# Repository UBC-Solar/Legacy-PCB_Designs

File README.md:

# PCB_Designs
Eagle files for PCBs designed for Raven

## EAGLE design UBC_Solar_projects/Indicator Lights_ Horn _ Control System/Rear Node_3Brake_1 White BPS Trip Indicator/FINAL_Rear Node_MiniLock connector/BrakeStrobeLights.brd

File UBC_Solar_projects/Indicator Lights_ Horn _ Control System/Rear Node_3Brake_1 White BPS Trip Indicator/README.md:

Rear Node Controls:
	1. 3 Brake Lights
	2. 1 White Strobe light (BPS TRIP INDICATOR)

NOTE:
	-PCB Holes are too close to sides
	-PCB Name should be on the buttom side

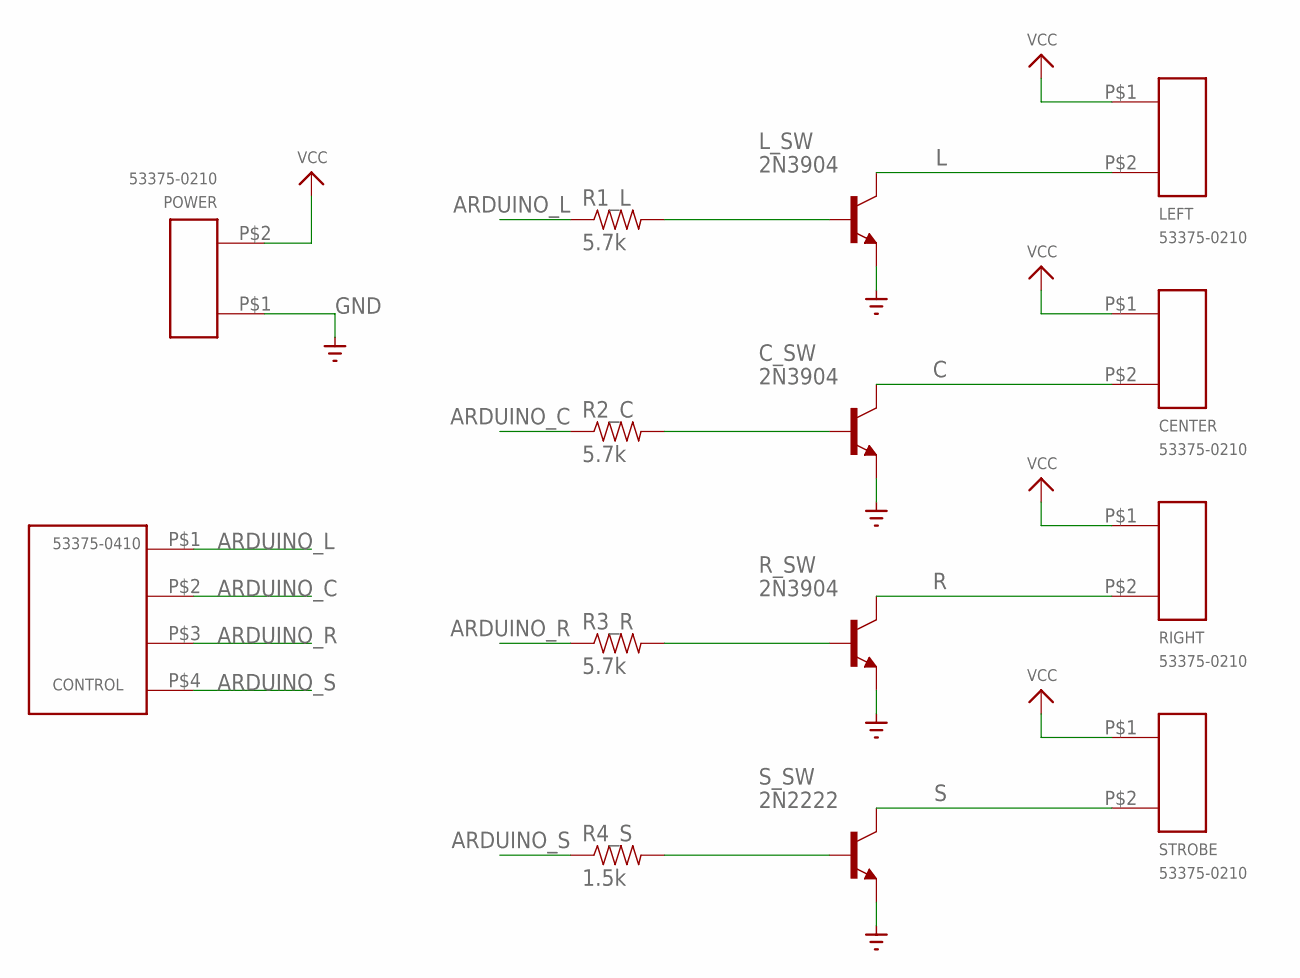
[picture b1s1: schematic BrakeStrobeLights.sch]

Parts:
CENTER: 53375-0210; 53375-0210-MINI-LOCK
CONTROL: 53375-0410; 53375-0410-MINI-LOCK
C_SW: 2N3904; TO92
LEFT: 53375-0210; 53375-0210-MINI-LOCK
L_SW: 2N3904; TO92
POWER: 53375-0210; 53375-0210-MINI-LOCK
R1_L, R2_C, R3_R: 5.7k; 1/6W-RES
R4_S: 1.5k; 1/6W-RES
RIGHT: 53375-0210; 53375-0210-MINI-LOCK
R_SW: 2N3904; TO92
STROBE: 53375-0210; 53375-0210-MINI-LOCK
S_SW: 2N2222; TO92-EBC-OVAL

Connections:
ARDUINO_C: CONTROL.P$2 (2), R2_C.1
ARDUINO_L: CONTROL.P$1 (1), R1_L.1
ARDUINO_R: CONTROL.P$3 (3), R3_R.1
ARDUINO_S: CONTROL.P$4 (4), R4_S.1
C: CENTER.P$2 (2), C_SW.1 (C)
GND: C_SW.3 (E), L_SW.3 (E), POWER.P$1 (1), R_SW.3 (E), S_SW.E
L: LEFT.P$2 (2), L_SW.1 (C)
unnamed: R3_R.2, R_SW.2 (B)
unnamed: C_SW.2 (B), R2_C.2
unnamed: R4_S.2, S_SW.B
unnamed: L_SW.2 (B), R1_L.2
R: RIGHT.P$2 (2), R_SW.1 (C)
S: STROBE.P$2 (2), S_SW.C
VCC: CENTER.P$1 (1), LEFT.P$1 (1), POWER.P$2 (2), RIGHT.P$1 (1), STROBE.P$1 (1)

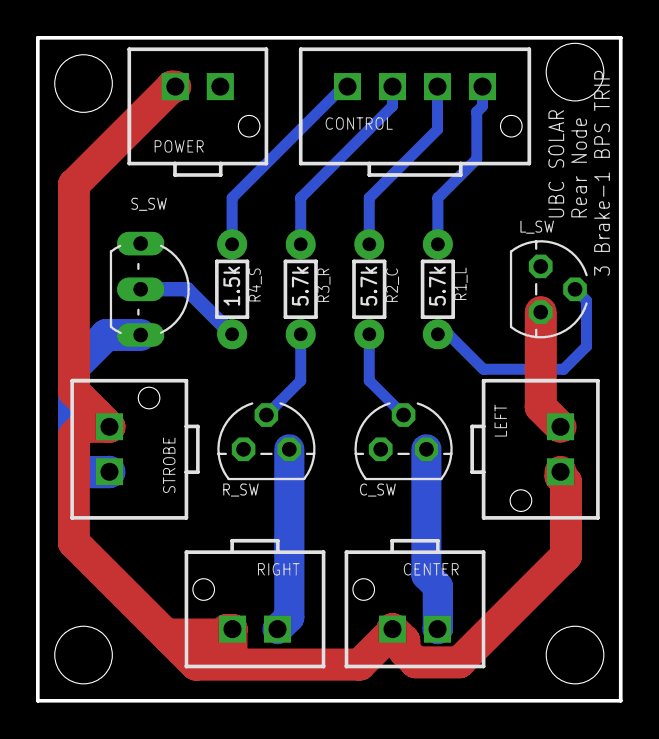
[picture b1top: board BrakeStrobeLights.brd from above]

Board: 2 copper layers, 32.4 x 36.8 mm, 14 parts (0 on the bottom side), 14 nets.

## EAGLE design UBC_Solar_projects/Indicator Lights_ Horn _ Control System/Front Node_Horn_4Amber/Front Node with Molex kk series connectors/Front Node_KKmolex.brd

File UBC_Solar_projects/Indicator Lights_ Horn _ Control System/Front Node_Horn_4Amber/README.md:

Front Node Controls:
	1. 4 Amber Lights
	2. Horn

NOTE:
	-PCB Holes are too close to sides
	-PCB Name should be on the buttom side

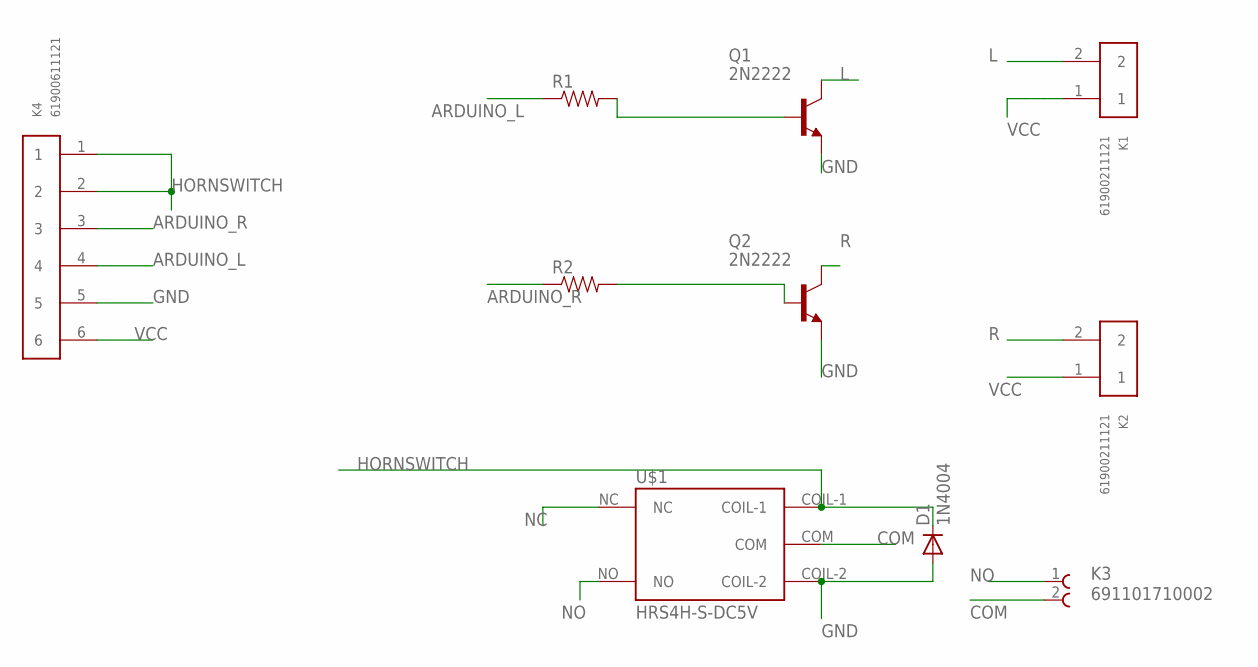
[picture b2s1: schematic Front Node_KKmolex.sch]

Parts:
D1: 1N4004; DO41-10
K1, K2: 61900211121
K3: 691101710002
K4: 61900611121
Q1, Q2: 2N2222; TO18
R1, R2: RESISTORPTH-1/4W; AXIAL-0.4
U$1: HRS4H-S-DC5V; RELAY

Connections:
ARDUINO_L: K4.4, R1.P$1 (1)
ARDUINO_R: K4.3, R2.P$1 (1)
COM: K3.2, U$1.COM
GND: D1.A, K4.5, Q1.1 (E), Q2.1 (E), U$1.COIL-2
HORNSWITCH: D1.C, K4.1, K4.2, U$1.COIL-1
L: K1.2, Q1.3 (C)
unnamed: Q2.2 (B), R2.P$2 (2)
unnamed: Q1.2 (B), R1.P$2 (2)
NC: U$1.NC
NO: K3.1, U$1.NO
R: K2.2, Q2.3 (C)
VCC: K1.1, K2.1, K4.6

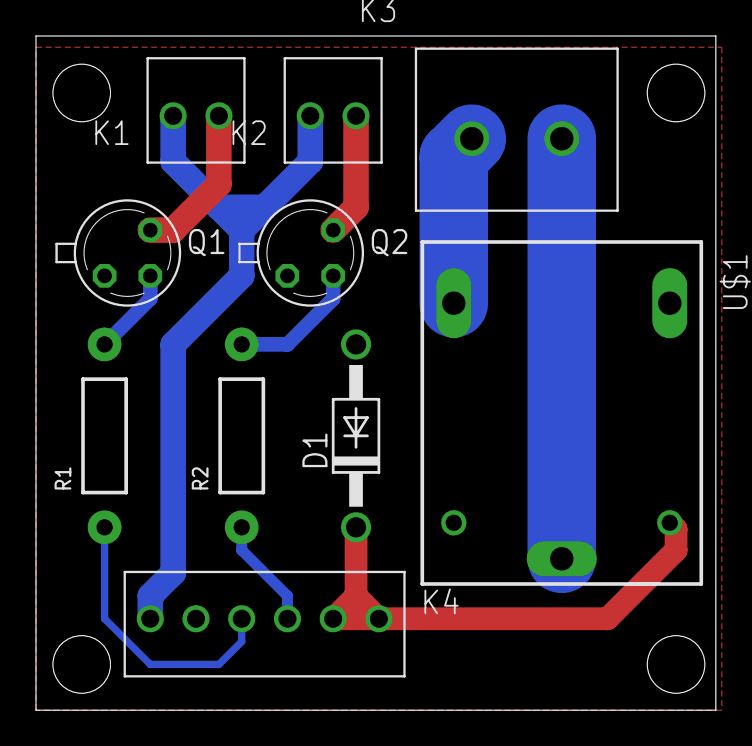
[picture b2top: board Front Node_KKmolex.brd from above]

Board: 2 copper layers, 37.8 x 37.5 mm, 10 parts (0 on the bottom side), 11 nets.

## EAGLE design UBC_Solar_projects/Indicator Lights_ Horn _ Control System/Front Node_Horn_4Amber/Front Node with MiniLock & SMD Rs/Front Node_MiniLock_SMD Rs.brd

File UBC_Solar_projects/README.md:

UBC Solar Projects.

Add this directory to your eagle project directory:
  1. choose "options" tab on eagle
  2. "Directory"
  3. Add the destination of this folder in your computer to the "Projects" list
  4. use semicolon ; to separate directories from each other when you have more than 1(in this case eagle default workspace and this folder)

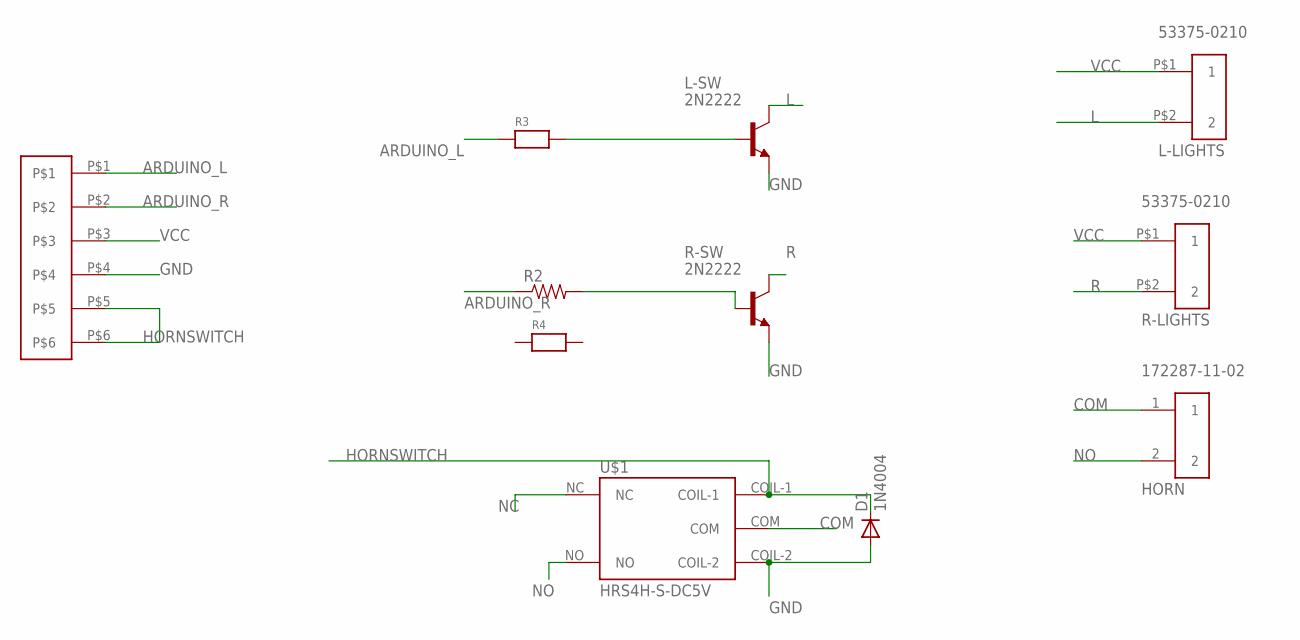
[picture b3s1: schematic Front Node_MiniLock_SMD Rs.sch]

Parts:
ARDUINO: 53375-0610; 53375-0610-MINI-LOCK
D1: 1N4004; DO41-10
HORN: 172287-11-02; 172287-ULTRA-FIT
L-LIGHTS: 53375-0210; 53375-0210-MINI-LOCK
L-SW: 2N2222; TO18
R2: RESISTORPTH-1/4W; AXIAL-0.4
R3, R4: RESISTOR1206; 1206
R-LIGHTS: 53375-0210; 53375-0210-MINI-LOCK
R-SW: 2N2222; TO18
U$1: HRS4H-S-DC5V; RELAY

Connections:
ARDUINO_L: ARDUINO.P$1, R3.1
ARDUINO_R: ARDUINO.P$2, R2.P$1 (1)
COM: HORN.1, U$1.COM
GND: ARDUINO.P$4, D1.A, L-SW.1 (E), R-SW.1 (E), U$1.COIL-2
HORNSWITCH: ARDUINO.P$5, ARDUINO.P$6, D1.C, U$1.COIL-1
L: L-LIGHTS.P$2 (2), L-SW.3 (C)
unnamed: R2.P$2 (2), R-SW.2 (B)
unnamed: L-SW.2 (B), R3.2
NC: U$1.NC
NO: HORN.2, U$1.NO
R: R-LIGHTS.P$2 (2), R-SW.3 (C)
VCC: ARDUINO.P$3, L-LIGHTS.P$1 (1), R-LIGHTS.P$1 (1)

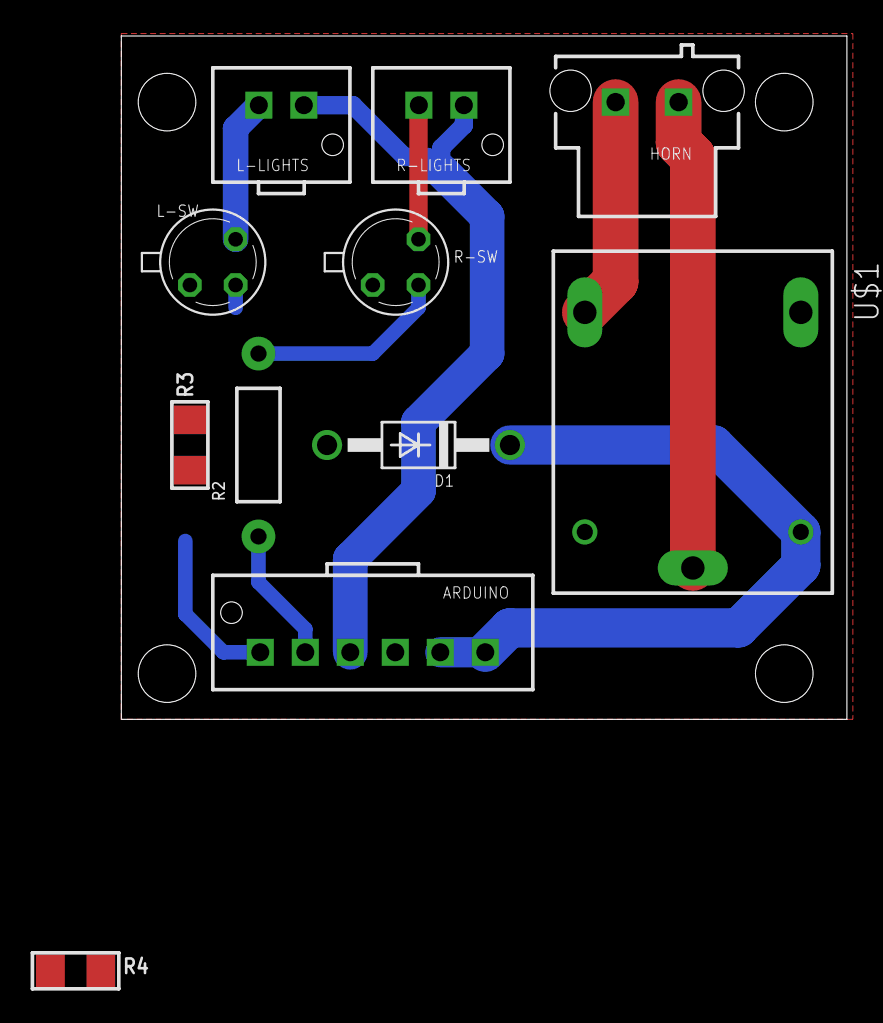
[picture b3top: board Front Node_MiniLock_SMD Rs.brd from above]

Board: 2 copper layers, 40.3 x 38.0 mm, 11 parts (0 on the bottom side), 11 nets.

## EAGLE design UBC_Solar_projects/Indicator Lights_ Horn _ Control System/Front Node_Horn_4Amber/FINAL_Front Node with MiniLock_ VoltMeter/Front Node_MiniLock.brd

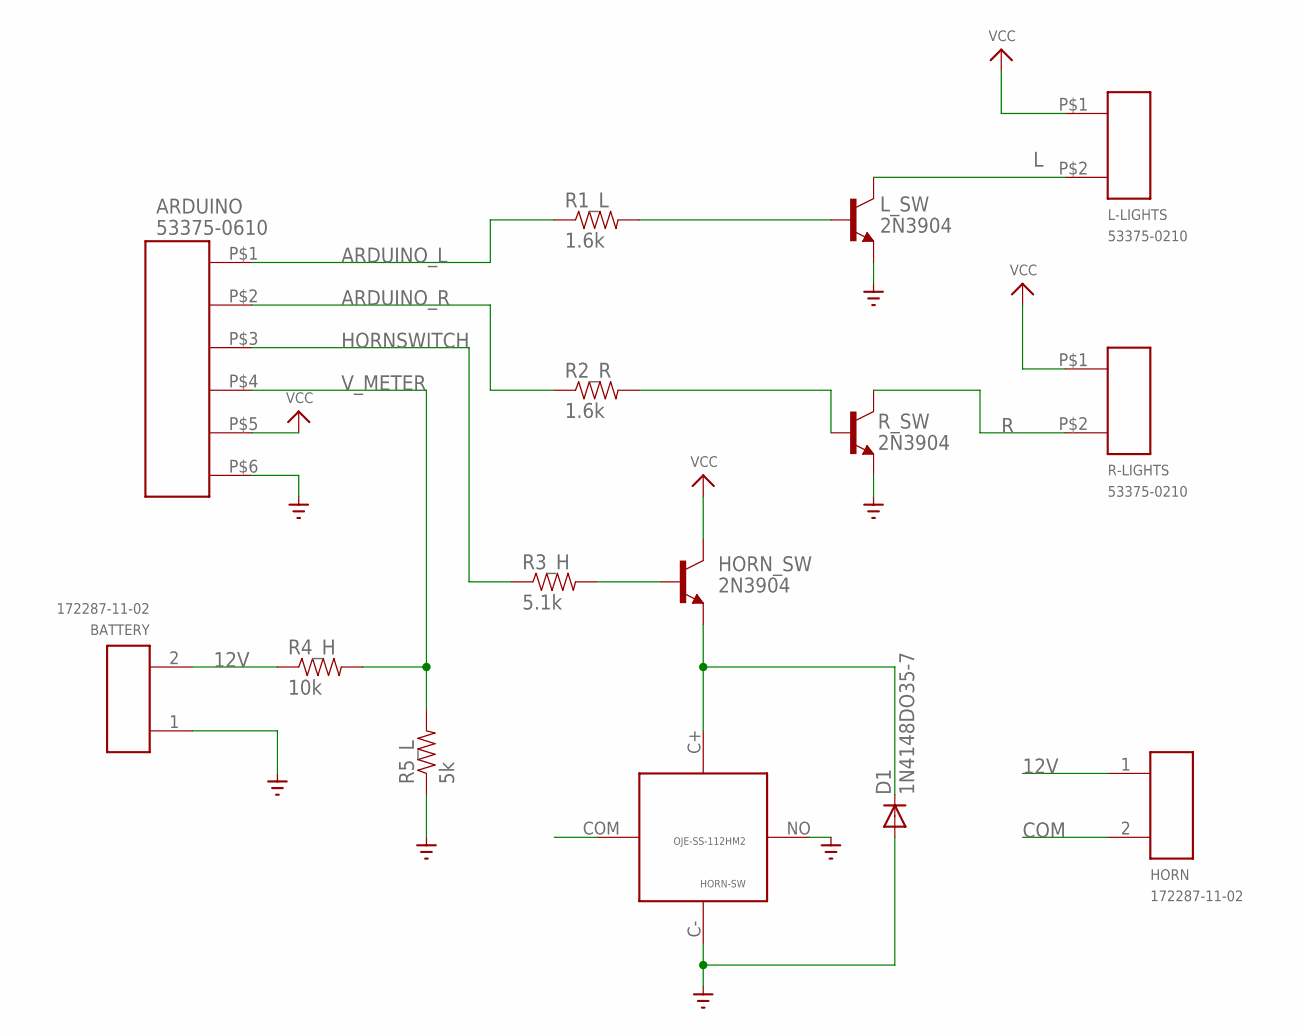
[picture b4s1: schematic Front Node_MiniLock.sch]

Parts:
ARDUINO: 53375-0610; 53375-0610-MINI-LOCK
BATTERY: 172287-11-02; 172287-ULTRA-FIT
D1: 1N4148DO35-7; DO35-7
HORN: 172287-11-02; 172287-ULTRA-FIT
HORN-SW: OJE-SS-112HM2; OJE-SS-112HM2-SPST-RELAY
HORN_SW: 2N3904; TO92
L-LIGHTS: 53375-0210; 53375-0210-MINI-LOCK
L_SW: 2N3904; TO92
R1_L, R2_R: 1.6k; 1/6W-RES
R3_H: 5.1k; 1/6W-RES
R4_H: 10k; 1/6W-RES
R5_L: 5k; 1/6W-RES
R-LIGHTS: 53375-0210; 53375-0210-MINI-LOCK
R_SW: 2N3904; TO92

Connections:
12V: BATTERY.2, HORN.1, R4_H.1
ARDUINO_L: ARDUINO.P$1, R1_L.1
ARDUINO_R: ARDUINO.P$2, R2_R.1
COM: HORN.2, HORN-SW.COM
GND: ARDUINO.P$6, BATTERY.1, D1.A, HORN-SW.C-, HORN-SW.NO, L_SW.3 (E), R5_L.1, R_SW.3 (E)
HORNSWITCH: ARDUINO.P$3, R3_H.1
L: L-LIGHTS.P$2 (2), L_SW.1 (C)
unnamed: HORN_SW.2 (B), R3_H.2
unnamed: R2_R.2, R_SW.2 (B)
unnamed: D1.C, HORN-SW.C+, HORN_SW.3 (E)
unnamed: L_SW.2 (B), R1_L.2
R: R-LIGHTS.P$2 (2), R_SW.1 (C)
VCC: ARDUINO.P$5, HORN_SW.1 (C), L-LIGHTS.P$1 (1), R-LIGHTS.P$1 (1)
V_METER: ARDUINO.P$4, R4_H.2, R5_L.2

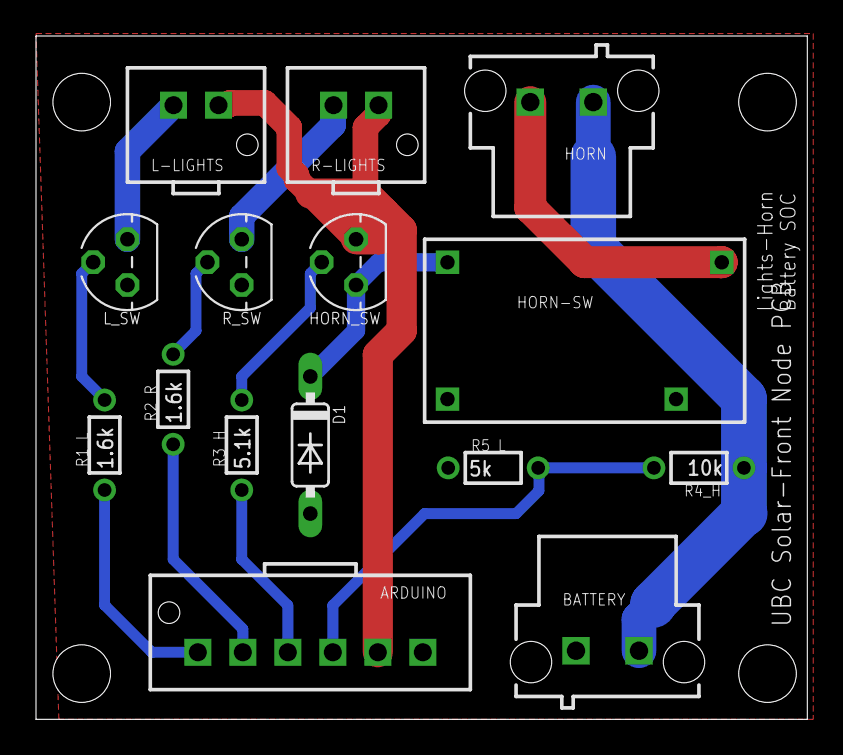
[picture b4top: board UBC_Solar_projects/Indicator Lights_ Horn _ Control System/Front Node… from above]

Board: 2 copper layers, 42.9 x 38.0 mm, 15 parts (0 on the bottom side), 14 nets.

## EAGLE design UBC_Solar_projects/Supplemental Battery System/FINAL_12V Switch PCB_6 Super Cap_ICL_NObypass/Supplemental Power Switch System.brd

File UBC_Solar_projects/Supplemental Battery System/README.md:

Supplemental Power Switch System:

1. ICL (inrush current limitter)
2. Backup Power Capacitor (supercapacitor)
3. Fused
4. Double Decker PCB

NOTE:
	-PCB Holes are too close to sides
	-PCB Name should be on the buttom side

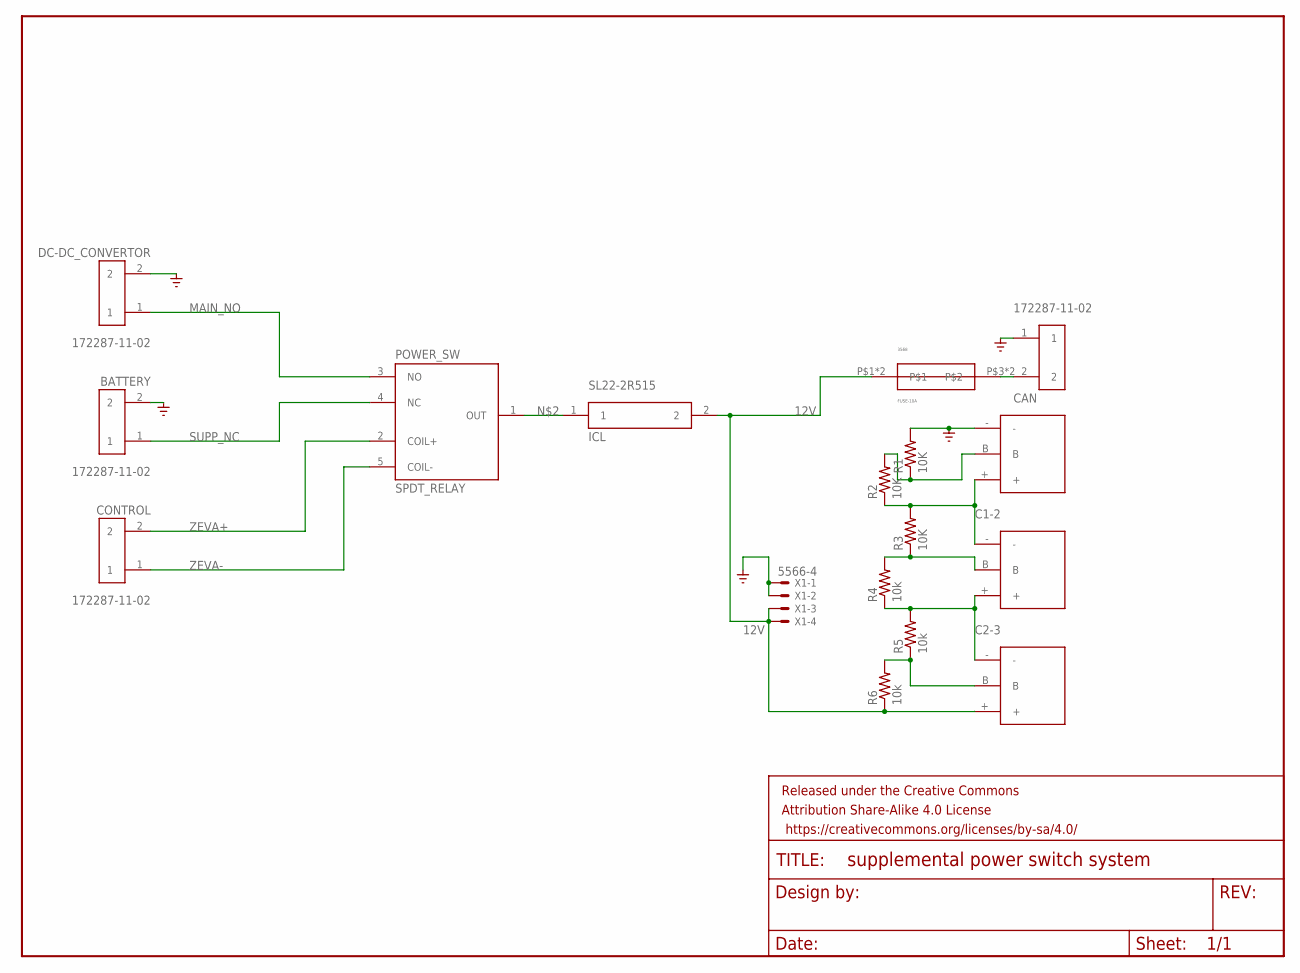
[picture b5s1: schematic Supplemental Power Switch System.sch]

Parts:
BATTERY: 172287-11-02; 172287-ULTRA-FIT
C1, C2, C3: SUPER-CAPACITOR; DMF
CAN: 172287-11-02; 172287-ULTRA-FIT
CONTROL: 172287-11-02; 172287-ULTRA-FIT
DC-DC_CONVERTOR: 172287-11-02; 172287-ULTRA-FIT
FRAME1: FRAME-LETTERNO_PACKAGE; DUMMY
FUSE-10A: 3568; 3568-MINI-297
ICL: SL22-2R515
POWER_SW: SPDT_RELAY; G8QN-1C4
R1, R2, R3: 10K; 1/6W-RES
R4, R5, R6: 10k; 1/6W-RES
X1: 5566-4

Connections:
12V: C3.+, FUSE-10A.P$1, FUSE-10A.P$2, ICL.2, R6.1, X1.3, X1.4
C1-2: C1.+, C2.-, R2.1, R3.2
C2-3: C2.+, C3.-, R4.1, R5.2
GND: BATTERY.2, C1.-, CAN.1, DC-DC_CONVERTOR.2, R1.2, X1.1, X1.2
MAIN_NO: DC-DC_CONVERTOR.1, POWER_SW.3 (NO)
unnamed: CAN.2, FUSE-10A.P$3, FUSE-10A.P$4
unnamed: ICL.1, POWER_SW.1 (OUT)
unnamed: C3.B, R5.1, R6.2
unnamed: C2.B, R3.1, R4.2
unnamed: C1.B, R1.1, R2.2
SUPP_NC: BATTERY.1, POWER_SW.4 (NC)
ZEVA+: CONTROL.2, POWER_SW.2 (COIL+)
ZEVA-: CONTROL.1, POWER_SW.5 (COIL-)

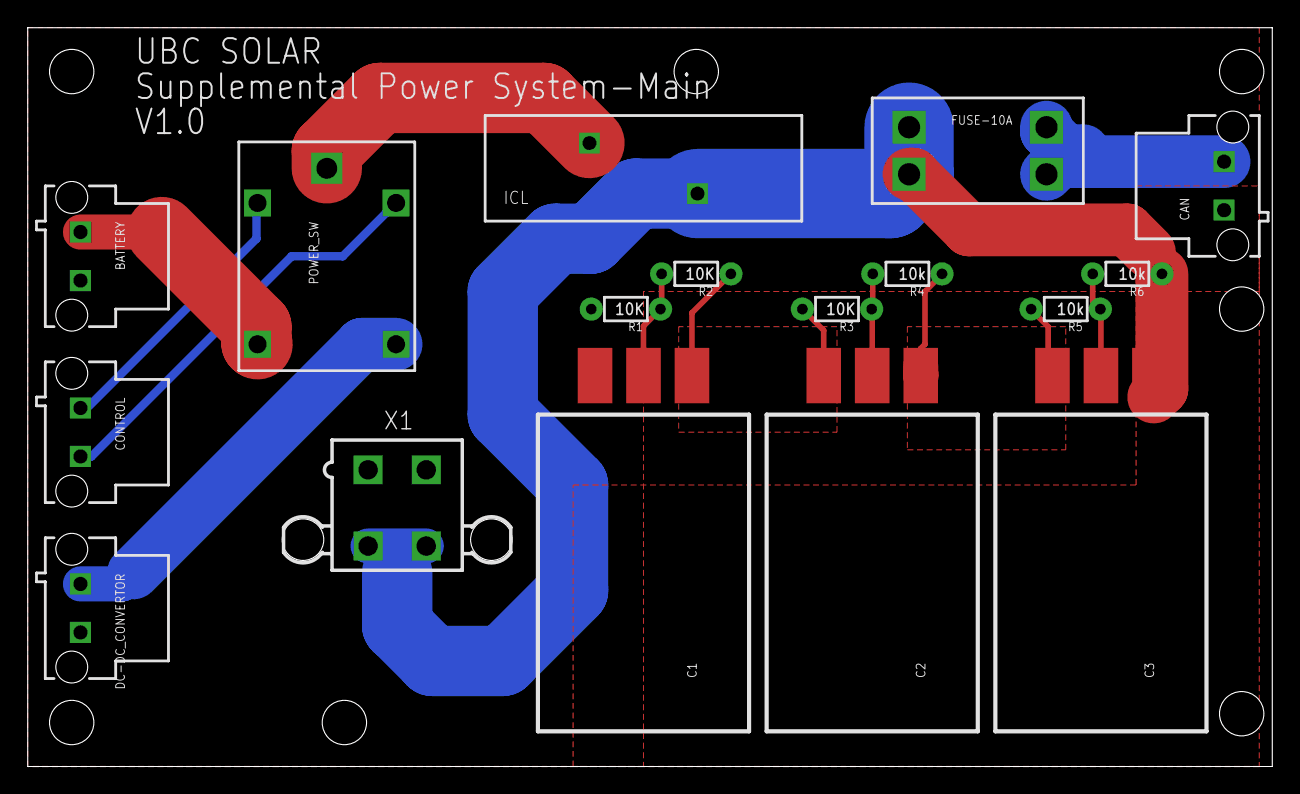
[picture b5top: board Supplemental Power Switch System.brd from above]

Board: 2 copper layers, 89.8 x 53.3 mm, 18 parts (0 on the bottom side), 13 nets.

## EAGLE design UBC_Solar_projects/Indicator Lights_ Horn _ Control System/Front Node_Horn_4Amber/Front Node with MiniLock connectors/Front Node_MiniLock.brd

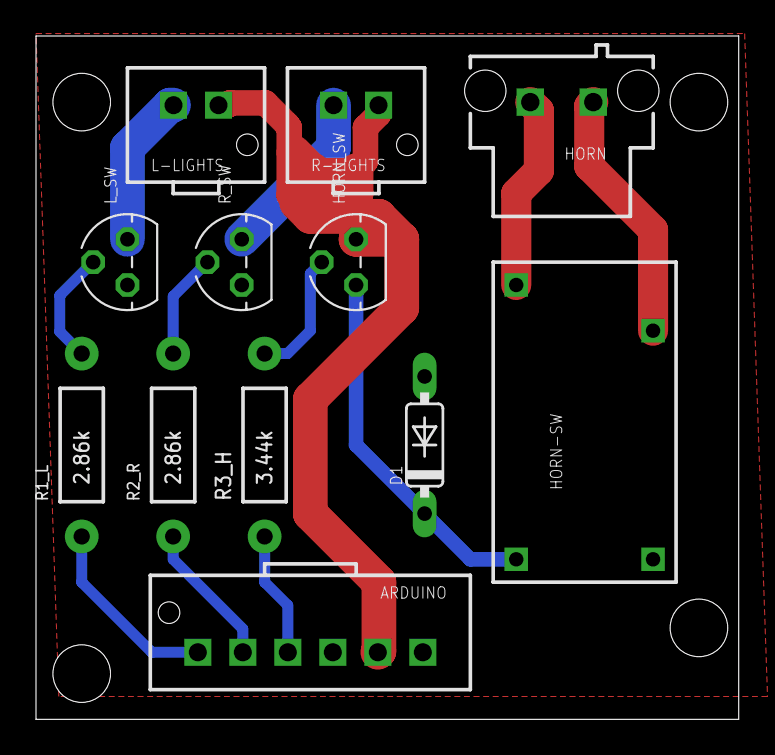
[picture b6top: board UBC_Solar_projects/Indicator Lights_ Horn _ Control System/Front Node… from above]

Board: 2 copper layers, 39.0 x 38.0 mm, 12 parts (0 on the bottom side), 13 nets.

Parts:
ARDUINO: 53375-0610; 53375-0610-MINI-LOCK
D1: 1N4148DO35-7; DO35-7
HORN: 172287-11-02; 172287-ULTRA-FIT
HORN-SW: OJE-SS-112HM2; OJE-SS-112HM2-SPST-RELAY
HORN_SW: 2N3904; TO92
L-LIGHTS: 53375-0210; 53375-0210-MINI-LOCK
L_SW: 2N3904; TO92
R1_L, R2_R: 2.86k; AXIAL-0.4
R3_H: 3.44k; AXIAL-0.4
R-LIGHTS: 53375-0210; 53375-0210-MINI-LOCK
R_SW: 2N3904; TO92

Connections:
ARDUINO_L: ARDUINO.P$1, R1_L.P$1
ARDUINO_R: ARDUINO.P$2, R2_R.P$1
COM: HORN.2, HORN-SW.COM
GND: ARDUINO.P$6, D1.A, HORN-SW.C-, L_SW.3, R_SW.3
HORNSWITCH: ARDUINO.P$3, R3_H.P$1
L: L-LIGHTS.P$2, L_SW.1
unnamed: HORN_SW.2, R3_H.P$2
unnamed: R2_R.P$2, R_SW.2
unnamed: D1.C, HORN-SW.C+, HORN_SW.3
unnamed: L_SW.2, R1_L.P$2
NO: HORN.1, HORN-SW.NO
R: R-LIGHTS.P$2, R_SW.1
VCC: ARDUINO.P$5, HORN_SW.1, L-LIGHTS.P$1, R-LIGHTS.P$1

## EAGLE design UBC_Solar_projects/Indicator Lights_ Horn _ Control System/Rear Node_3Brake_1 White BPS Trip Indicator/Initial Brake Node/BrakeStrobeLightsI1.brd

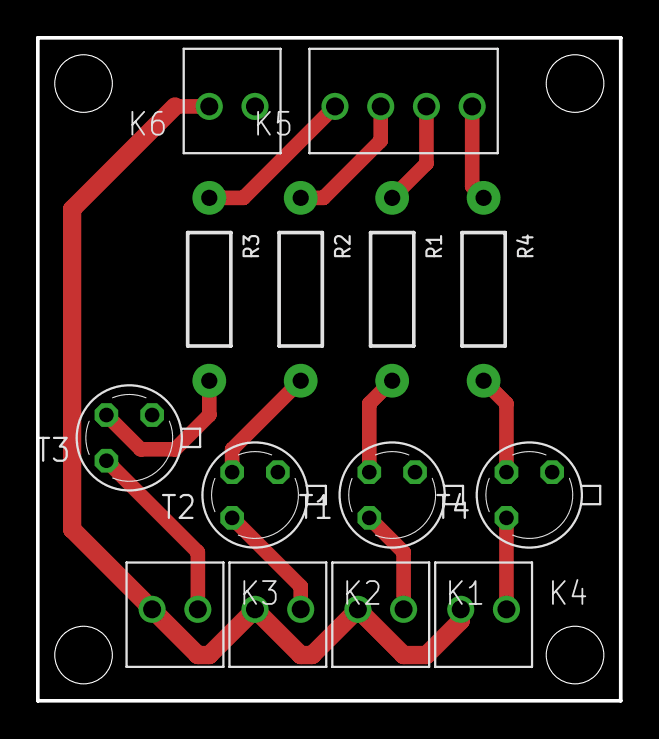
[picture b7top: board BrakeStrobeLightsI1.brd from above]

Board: 2 copper layers, 32.4 x 36.8 mm, 14 parts (0 on the bottom side), 14 nets.

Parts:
K1, K2, K3, K4, K6: 61900211121
K5: 61900411121
R1, R2, R3, R4: AXIAL-0.4
T1, T2, T3, T4: 2N2222; TO18

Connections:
ARDUINO_C: K5.2, R2.P$1
ARDUINO_L: K5.3, R1.P$1
ARDUINO_R: K5.1, R3.P$1
ARDUINO_S: K5.4, R4.P$1
C: K2.1, T2.3
GND: K6.2, T1.1, T2.1, T3.1, T4.1
L: K1.1, T1.3
unnamed: R3.P$2, T3.2
unnamed: R2.P$2, T2.2
unnamed: R4.P$2, T4.2
unnamed: R1.P$2, T1.2
R: K3.1, T3.3
S: K4.1, T4.3
VCC: K1.2, K2.2, K3.2, K4.2, K6.1

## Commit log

2017-02-18 Supplemental Battery Switch System PCB Design
2017-02-19 Front Node PCB with Molex KK connectors and Terminal Blocks.
2017-02-19 Readme added for both front and rear nodes
2017-02-19 Front Node double Layered. Board is smaller
2017-02-19 some modification
2017-02-25 added the libraries for some parts used in projects
2017-02-25 Update README.md
    Instructions for how to include library to your eagle
2017-02-25 separated project folder from library folder
2017-02-25 Instructions to add the projects folder to eagle directory
2017-03-04 added Mini-Fit Receptacle Header to custom library
2017-03-04 added current PCB files for MPPT and rear brake node
2017-03-04 Added folders containing files for rear brake node and MPPT
2017-03-05 Added MiniLock connectors to custom library
2017-03-05 changed fron node connectors with MiniLock. Rear Node SCH REQUIRED.
2017-03-18 Couldnt find edited brake node files, need to edit them again then recommit
2017-03-18 I1 is current iteration of brake strobe lights
2017-03-19 footprint for fuseholder is added
2017-03-21 added the SPST relay to library
2017-03-22 Front Node Ready. Supports Indicator lights, Horn, Voltmeter (for battery)
2017-03-22 Rear Node Ready. 4 switches, MiniLock Connectors
2017-03-25 Library Modification. Supplemental Power System modification
2017-03-25 Adding new MPPT folder with project
2017-03-25 Keep-out layers added to MPPT PCB files
2017-03-25 Library Modification, Supplemental Power PCB refinement
2017-03-26 Supplemental Power PCB Finalized
2017-03-26 Supplemental Power PCB : Capacitor PCB Extension refinement
2017-04-01 Some Minor Changes in the files.
2017-04-03 Gerber files added. under audit by PCBway
2017-04-03 Fixed Gerber files for MPPT pcb
2017-04-06 Finally all PCBs got approved
2017-04-14 modified some files. Fixed a mistake (pad size) in SPST relay footprint
2017-10-14 PCB Designs V2

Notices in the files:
parts and their libraries:
SparkFun-Passives: Licensing: Creative Commons ShareAlike 4.0 International - https://creativecommons.org/licenses/by-sa/4.0
microbuilder: This work is placed in the public domain, and may be freely used for commercial and non-commercial work with the following conditions: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
